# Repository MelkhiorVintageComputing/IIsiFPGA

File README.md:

# A FPGA on a IIsi PDS card...

## Goal

The goal of this repository is to be able to interface a modern (2023 era) [FPGA](https://en.wikipedia.org/wiki/Field-programmable_gate_array) with a [Macintosh IIsi](https://en.wikipedia.org/wiki/Macintosh_IIsi) using its PDS (Processor Direct Slot) connector. The PDS is basically just a physical connector to the MC68030 memory bus.

So unless you're a retrocomputing enthusiast with such a machine, this is useless. If you are such an enthusiast, then maybe the ability to connect a modern LCD monitor using a digital interface to an old Macintosh might be of interest to you.

This project was 'spun off' the [NuBusFPGA](https://github.com/rdolbeau/NuBusFPGA), a similar project for the NuBus used in several models of Macintosh of the era. NuBusFPGA itself is a spin-off of the [SBusFPGA](https://github.com/rdolbeau/SBusFPGA), a similar project for the SBus used in Sun's SPARCstation.

## Current status

The HDMI (Highly Desirable Macintosh Interface) is working, with both video (single-hardware-res, multi-depth, windowboxed lower res) & audio working. More details are available in the readme of the NuBusFPGA repository.

There's also experimental support to expose 240 MiB of DDR3 as additional memory to the host system, but that requires a patched ROM, typically using a modern Flash-based 'ROM SIMM'. Burst reads are supported for that use case, reading 16 bytes at a time from the DDR3 using a dedicated port, giving X-1-1-1 burst timings.

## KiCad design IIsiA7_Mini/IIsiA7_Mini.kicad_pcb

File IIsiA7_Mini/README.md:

# IIsiA7 Mini

## Known issues in V3.0

* The JTAG header is not wired as intended (doesn't follow any pinouts I know), but the silkscreen is correct and it can be used just fine
* Pinout silkscreen for leds D4 and D5 is switched (D4 <=> D6), D6 is really top and D4 bottom)
* IRQs and CACHE should have had pull (up for IRQs, down for CACHE), the gateware currently enables pulling at the FPGA pins

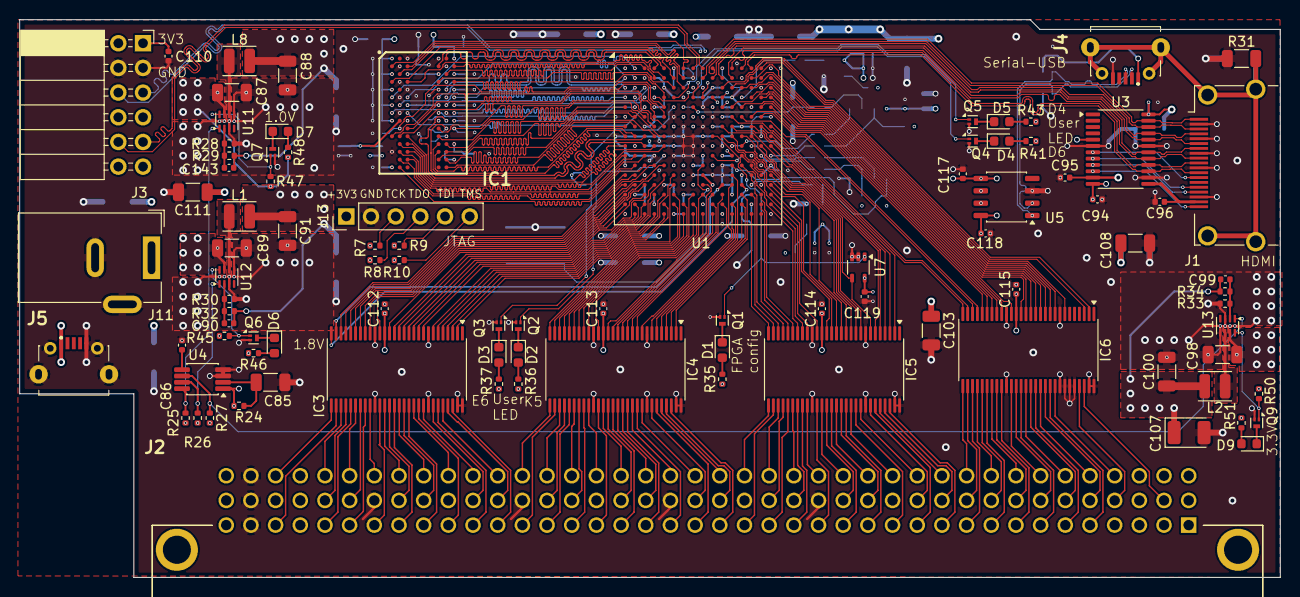
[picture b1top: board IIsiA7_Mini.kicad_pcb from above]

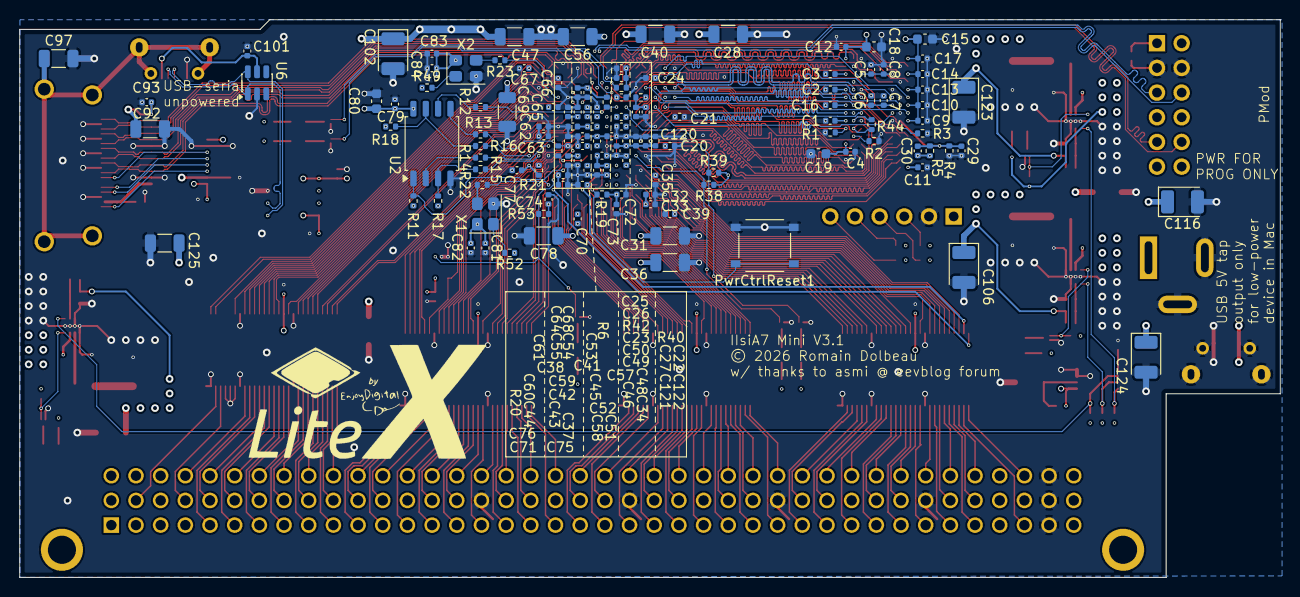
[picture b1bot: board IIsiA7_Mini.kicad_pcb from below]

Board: 6 copper layers, 129.8 x 57.4 mm, 221 parts (130 on the bottom side), 326 nets.

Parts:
C1, C2, C3, C4, C5, C6, C7, C8, C9, C10, C11, C12, C13, C14, C16, C17, C29, C30, C79, C81, C82, C83, C84, C94, C95, C96, C101, C110, C112, C113, C114, C115, C117, C118, C119: 100nF 0402; C_0402_1005Metric
C15, C18, C19, C80: 1uF 0603; C_0603_1608Metric
C20, C21, C22, C23, C24, C25, C31, C33, C34, C35, C37, C41, C42, C43, C45, C48, C49, C50, C51, C52, C53, C54, C55, C60, C63, C65, C66, C67, C68, C70, C72, C74, C75, C76, C77, C121: 470nF 0402; C_0402_1005Metric
C26, C27, C32, C38, C44, C46, C57, C58, C59, C61, C62, C64, C71, C73, C120, C122: 4.7uF 0402; C_0402_1005Metric
C28, C36, C39, C40, C47, C56, C69, C78: 100uF 1206; C_1206_3216Metric
C85, C87, C88, C89, C91, C93, C98, C100, C103, C108, C111, C125: 22uF 25V 1206; C_1206_3216Metric
C86, C92: 10nF 0402; C_0402_1005Metric
C90, C99, C143: 120pF C0G 0402; C_0402_1005Metric
C97: 1nF >=1kV 1206; C_1206_3216Metric
C102, C106, C123: 330uF CASE-B Tantalum 2.5V; CP_EIA-3528-21_Kemet-B
C107, C116, C124: 150uF CASE-B Tantalum 6.3V; CP_EIA-3528-21_Kemet-B
D1, D2, D3, D4, D5, D6, D7, D9: LED 0603; LED_0603_1608Metric
GRAPHIC1: LogoLitex; litex_logo
IC1: MT47H128M16RT-25E_C_TR; BGA84C80P9X15_900X1250X120
IC3, IC4, IC5, IC6: 74CB3T16211DGGR; TSSOP-56_6.1x14mm_P0.5mm
J1: 10029449-111RLF (HDMI A); HDMI_A_Amphenol_10029449-111
J2: 650906-5; 6509065
J3: PMod 2x6 pins, 2.54mm 90° socket; PinSocket_2x06_P2.54mm_Horizontal
J4, J5: USB Micro-B; MICROXNJ
J11: Barrel_Jack_Switch; BarrelJack_Wuerth_6941xx301002
J13: Conn_01x06_Pin; PinHeader_1x06_P2.54mm_Vertical
L1, L2, L8: 470nH 6.5A 322512; L_Changjiang_FTC322512S
PwrCtrlReset1: TS-1187A-B-A-B; SW_SPST_TS-1187A
Q1, Q2, Q3, Q4, Q5, Q6, Q7, Q9: AP1606; Diodes_DFN1006-3
R1, R2, R3, R11, R17, R18, R19, R20, R53: 4.7kΩ 0402; R_0402_1005Metric
R4, R5: 1kΩ 0402 0.1%; R_0402_1005Metric
R6, R21, R49, R52: 0Ω 0402; R_0402_1005Metric
R7, R8, R9, R10, R24, R38, R39, R40, R42, R45, R47, R50: 10kΩ 0402; R_0402_1005Metric
R12, R13, R14, R15, R16: 49.9Ω 0402 1%; R_0402_1005Metric
R22, R23: 33Ω 0402 1%; R_0402_1005Metric
R25, R26, R27: 100kΩ 0402; R_0402_1005Metric
R28: 66.5kΩ 0402 0.1%; R_0402_1005Metric
R29, R32, R34: 100kΩ 0402 0.1%; R_0402_1005Metric
R30: 200kΩ 0402 0.1%; R_0402_1005Metric
R31: 1MΩ 500V 1206; R_1206_3216Metric
R33: 453kΩ 0402 0.1%; R_0402_1005Metric
R35, R36, R37, R41, R43: 510Ω 0402; R_0402_1005Metric
R44: 100Ω 0402 0.1%; R_0402_1005Metric
R46, R48, R51: 1kΩ 0402; R_0402_1005Metric
U1: XC7A100T-FTG256; Xilinx_FTG256
U2: W25Q128JVS; SOIC-8_5.3x5.3mm_P1.27mm
U3: TPD12S016PWR; TSSOP-24_4.4x7.8mm_P0.65mm
U4: LM3881MM; VSSOP-8_3x3mm_P0.65mm
U5: CH340N; JEITA_SOIC-8_3.9x4.9mm_P1.27mm
U6: SRV05-4; SOT-23-6
U7: 74LVC1G125DCK; Texas_R-PDSO-G5_DCK-5
U11, U12, U13: TPS62823DLCR; Texas_VSON-HR-8_1.5x2mm_P0.5mm
X1, X2: ASE-xxxMHz; Oscillator_SMD_Abracon_ASE-4Pin_3.2x2.5mm

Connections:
+1V0: C45.1, C46.1, C47.1, C48.1, C49.1, C50.1, C51.1, C52.1, C53.1, C54.1, C55.1, C56.1, C57.1, C58.1, C59.1, C61.1, C88.1, C102.1, C120.1, C121.1, C122.1, C123.1, C143.2, L8.2, R28.2, U1.E10 (VCCBRAM), U1.F7 (VCCINT), U1.F9 (VCCINT), U1.F11 (VCCBRAM), U1.G6 (VCCINT), U1.H9 (VCCINT), U1.J6 (VCCINT), U1.K9 (VCCINT), U1.L8 (VCCINT)
+1V8: C1.1, C2.1, C3.1, C4.1, C5.1, C6.1, C7.1, C8.1, C9.1, C10.1, C11.1, C12.1, C13.1, C14.1, C15.1, C16.1, C17.1, C18.1, C19.1, C20.1, C21.1, C22.1, C23.1, C24.1, C25.1, C26.1, C27.1, C28.1, C30.1, C37.1, C38.1, C40.1, C41.1, C42.1, C43.1, C44.1, C90.2, C91.1, C106.1, IC1.A1 (VDD_1), IC1.A9 (VDDQ_1), IC1.C1 (VDDQ_2), IC1.C3 (VDDQ_3), IC1.C7 (VDDQ_4), IC1.C9 (VDDQ_5), IC1.E1 (VDD_2), IC1.E9 (VDDQ_6), IC1.G1 (VDDQ_7), IC1.G3 (VDDQ_8), IC1.G7 (VDDQ_9), IC1.G9 (VDDQ_10), IC1.J1 (VDDL), IC1.J9 (VDD_3), IC1.M9 (VDD_4), IC1.R1 (VDD_5), L1.2, R5.1, R30.2, R38.1, R39.1, R40.1, R42.1, U1.A6 (VCCO_35), U1.B3 (VCCO_35), U1.D7 (VCCO_35), U1.E4 (VCCO_35), U1.F1 (VCCO_35), U1.F8 (VCCBATT_0), U1.G8 (VCCADC_0), U1.G10 (VCCAUX), U1.J2 (VCCO_35), U1.J10 (VCCAUX), U1.K11 (VCCAUX), U1.L10 (VCCAUX)
+3V3: C31.1, C32.1, C33.1, C34.1, C35.1, C36.1, C39.1, C60.1, C62.1, C63.1, C64.1, C65.1, C66.1, C67.1, C68.1, C69.1, C70.1, C71.1, C72.1, C73.1, C74.1, C75.1, C76.1, C77.1, C78.1, C79.1, C80.1, C81.1, C82.1, C83.1, C84.1, C92.1, C93.1, C94.1, C99.2, C100.1, C103.1, C107.1, C108.1, C110.1, C111.1, C112.1, C113.1, C114.1, C115.1, C117.1, C118.1, C119.1, C125.1, IC3.17 (VCC), IC4.17 (VCC), IC5.17 (VCC), IC6.17 (VCC), J3.1, J3.2, J13.1, L2.2, R6.2, R7.1, R8.1, R9.1, R10.1, R11.2, R17.2, R18.2, R19.2, R20.2, R21.2, R33.2, R35.2, R36.2, R37.2, R41.2, R43.2, R49.1, R52.1, R53.2, U1.A16 (VCCO_15), U1.B13 (VCCO_15), U1.C10 (VCCO_15), U1.E14 (VCCO_15), U1.H15 (VCCO_15), U1.J12 (VCCO_15), U1.L6 (VCCO_0), U1.L16 (VCCO_14), U1.M3 (VCCO_34), U1.M9 (M0_0), U1.M13 (VCCO_14), U1.N10 (VCCO_14), U1.P7 (VCCO_14), U1.R4 (VCCO_34), U1.R14 (VCCO_14), U1.T1 (VCCO_34), U1.T11 (VCCO_14), U2.8 (VCC), U3.5 (LS_OE), U3.12 (CT_HPD), U3.24 (VCCA), U5.5 (VCC), U5.8 (V3), U7.5 (VCC), X1.4 (Vdd), X2.4 (Vdd)
+5V: C87.1, C89.1, C95.1, C98.1, C116.1, C124.1, J2.A37, J2.B13, J2.B19, J2.B25, J2.B31, J2.B37, J2.C37, J5.1 (VBUS), J11.1, R24.2, R25.2, R26.2, R27.2, R45.1, R46.2, R47.1, R48.2, R50.1, R51.2, U3.11 (VCC5V), U4.1 (VCC), U11.7 (VIN), U12.7 (VIN), U13.7 (VIN)
/Artix-7 Bank 14+15/CLK_54_000: R23.1, U1.D13 (IO_L12P_T1_MRCC_15)
/Artix-7 Bank 14+15/CLK_100_000: R22.1, U1.N14 (IO_L12P_T1_MRCC_14)
/Artix-7 Bank 34+35/IO_0_35: Q3.1 (G), R39.2, U1.E6 (IO_0_35)
/Artix-7 Bank 34+35/IO_25_35: Q2.1 (G), R38.2, U1.K5 (IO_25_35)
/Artix-7 Bank 34+35/IO_L6P_T0_35: Q5.1 (G), R42.2, U1.D6 (IO_L6P_T0_35)
/Artix-7 Bank 34+35/IO_L12P_T1_MRCC_35: Q4.1 (G), R40.2, U1.D4 (IO_L12P_T1_MRCC_35)
/Artix-7 Bank 34+35/ddr2/DDR2_CS: IC1.L8 (CS#), R2.1
/Artix-7 Support/CCLK_0: R12.1, U1.E8 (CCLK_0)
/Artix-7 Support/FPGA flash/CLK: R12.2, U2.6 (CLK)
/Artix-7 Support/FPGA flash/IO_{0}: R13.2, U2.5 (DI/IO_{0})
/Artix-7 Support/FPGA flash/IO_{1}: R14.2, U2.2 (DO/IO_{1})
/Artix-7 Support/FPGA flash/IO_{2}: R15.2, R17.1, U2.3 (~WP/IO_{2})
/Artix-7 Support/FPGA flash/IO_{3}: R16.2, R18.1, U2.7 (~HOLD/~RESET/IO_{3})
/Artix-7 Support/INIT_B_0: R20.1, U1.K10 (INIT_B_0)
/Artix-7 Support/PROGRAM_B_0: PwrCtrlReset1.1, R19.1, U1.L9 (PROGRAM_B_0)
/Artix-7 Support/TCK_0: J13.3, R7.2, U1.L7 (TCK_0)
/Artix-7 Support/TDI_0: J13.5, R9.2, U1.N7 (TDI_0)
/Artix-7 Support/TDO_0: J13.4, R8.2, U1.N8 (TDO_0)
/Artix-7 Support/TMS_0: J13.6, R10.2, U1.M7 (TMS_0)
/Board Specific/HDMI (Highly Desirable Macintosh Interface)/HDMI_5V: C96.1, J1.18 (+5V), U3.13 (5V_OUT)
/Board Specific/HDMI (Highly Desirable Macintosh Interface)/HDMI_CEC_B: J1.13 (CEC), U3.7 (CEC_B)
/Board Specific/HDMI (Highly Desirable Macintosh Interface)/HDMI_HPD_B: J1.19 (HPD), U3.10 (HPD_B)
/Board Specific/HDMI (Highly Desirable Macintosh Interface)/HDMI_SCL_B: J1.15 (SCL), U3.8 (SCL_B)
/Board Specific/HDMI (Highly Desirable Macintosh Interface)/HDMI_SDA_B: J1.16 (SDA), U3.9 (SDA_B)
/Board Specific/serial_usb/USB_D+: J4.3 (D+), U5.1 (UD+), U6.6 (IO4)
/Board Specific/serial_usb/USB_D-: J4.2 (D-), U5.2 (UD-), U6.1 (IO1)
/Board Specific/serial_usb/Vbus: C101.1, J4.1 (VBUS), U6.5 (VP)
/FLAG1: R25.1, U4.8 (FLAG1), U11.1 (EN)
/FLAG2: R26.1, U4.7 (FLAG2), U12.1 (EN)
/FLAG3: R27.1, U4.6 (FLAG3), U13.1 (EN)
/PWRGOOD_1V0: Q7.1 (G), R47.2, U11.8 (PG)
/PWRGOOD_1V8: Q6.1 (G), R45.2, U12.8 (PG)
/PWRGOOD_3V3: Q9.1 (G), R50.2, U13.8 (PG)
/PWRGOOD_5V: C85.1, R24.1, U4.2 (EN)
/power_rail_1V0/FB: C143.1, R28.1, R29.2, U11.2 (FB)
/power_rail_1V0/SW: L8.1, U11.6 (SW)
/power_rail_1V8/FB: C90.1, R30.1, R32.2, U12.2 (FB)
/power_rail_1V8/SW: L1.1, U12.6 (SW)
/power_rail_3V3/FB: C99.1, R33.1, R34.2, U13.2 (FB)
/power_rail_3V3/SW: L2.1, U13.6 (SW)
A0_3V3: IC3.26 (2A10), U1.M1 (IO_L2N_T0_34)
A0_5V: IC3.31 (2B10), J2.C36
A1_3V3: IC3.25 (2A9), U1.M2 (IO_L2P_T0_34)
A1_5V: IC3.32 (2B9), J2.B36
A2_3V3: IC3.24 (2A8), U1.L4 (IO_L1P_T0_34)
A2_5V: IC3.33 (2B8), J2.A36
A3_3V3: IC3.23 (2A7), U1.N1 (IO_L4P_T0_34)
A3_5V: IC3.34 (2B7), J2.C35
A4_3V3: IC3.22 (2A6), U1.L5 (IO_0_34)
A4_5V: IC3.35 (2B6), J2.B35
A5_3V3: IC3.21 (2A5), U1.N2 (IO_L3N_T0_DQS_34)
A5_5V: IC3.36 (2B5), J2.A35
A6_3V3: IC3.20 (2A4), U1.P1 (IO_L4N_T0_34)
A6_5V: IC3.37 (2B4), J2.C34
A7_3V3: IC3.18 (2A3), U1.M4 (IO_L1N_T0_34)
A7_5V: IC3.39 (2B3), J2.A34
A8_3V3: IC3.16 (2A2), U1.N3 (IO_L3P_T0_DQS_34)
A8_5V: IC3.40 (2B2), J2.C33
A9_3V3: IC3.15 (2A1), U1.R1 (IO_L7N_T1_34)
A9_5V: IC3.41 (2B1), J2.B33
A10_3V3: IC3.14 (1A12), U1.P3 (IO_L5N_T0_34)
A10_5V: IC3.42 (1B12), J2.A33
A11_3V3: IC3.13 (1A11), U1.N4 (IO_L6N_T0_VREF_34)
A11_5V: IC3.43 (1B11), J2.C32
A12_3V3: IC3.12 (1A10), U1.T2 (IO_L8N_T1_34)
A12_5V: IC3.44 (1B10), J2.B32
A13_3V3: IC3.11 (1A9), U1.R2 (IO_L7P_T1_34)
A13_5V: IC3.45 (1B9), J2.A32
A14_3V3: IC3.10 (1A8), U1.R3 (IO_L8P_T1_34)
A14_5V: IC3.46 (1B8), J2.C31
A15_3V3: IC3.9 (1A7), U1.T3 (IO_L9N_T1_DQS_34)
A15_5V: IC3.47 (1B7), J2.A31
A16_3V3: IC3.7 (1A6), U1.M5 (IO_L6P_T0_34)
A16_5V: IC3.48 (1B6), J2.C30
A17_3V3: IC3.6 (1A5), U1.P4 (IO_L5P_T0_34)
A17_5V: IC3.50 (1B5), J2.B30
A18_3V3: IC3.5 (1A4), U1.T4 (IO_L9P_T1_DQS_34)
A18_5V: IC3.51 (1B4), J2.A30
A19_3V3: IC3.4 (1A3), U1.P5 (IO_L10P_T1_34)
A19_5V: IC3.52 (1B3), J2.C29
A20_3V3: IC3.3 (1A2), U1.M6 (IO_L19P_T3_A10_D26_14)
A20_5V: IC3.53 (1B2), J2.B29
A21_3V3: IC3.2 (1A1), U1.T5 (IO_L23N_T3_A02_D18_14)
A21_5V: IC3.54 (1B1), J2.A29
A22_3V3: IC4.28 (2A12), U1.R5 (IO_L23P_T3_A03_D19_14)
A22_5V: IC4.29 (2B12), J2.C28
A23_3V3: IC4.27 (2A11), U1.N6 (IO_L19N_T3_A09_D25_VREF_14)
A23_5V: IC4.30 (2B11), J2.A28
A24_3V3: IC4.26 (2A10), U1.R6 (IO_L24P_T3_A01_D17_14)
A24_5V: IC4.31 (2B10), J2.C27
A25_3V3: IC4.25 (2A9), U1.P6 (IO_25_14)
A25_5V: IC4.32 (2B9), J2.B27
A26_3V3: IC4.24 (2A8), U1.T7 (IO_L21P_T3_DQS_14)
A26_5V: IC4.33 (2B8), J2.A27
A27_3V3: IC4.23 (2A7), U1.R7 (IO_L24N_T3_A00_D16_14)
A27_5V: IC4.34 (2B7), J2.C26
A28_3V3: IC4.22 (2A6), U1.P8 (IO_L20P_T3_A08_D24_14)
A28_5V: IC4.35 (2B6), J2.B26
A29_3V3: IC4.21 (2A5), U1.T8 (IO_L21N_T3_DQS_A06_D22_14)
A29_5V: IC4.36 (2B5), J2.A26
A30_3V3: IC4.20 (2A4), U1.R8 (IO_L20N_T3_A07_D23_14)
A30_5V: IC4.37 (2B4), J2.C25
A31_3V3: IC4.18 (2A3), U1.P9 (IO_L18N_T2_A11_D27_14)
A31_5V: IC4.39 (2B3), J2.A25
APMOD0-56+: J3.6, U1.E11 (IO_L14P_T2_SRCC_15)
APMOD0-56-: J3.5, U1.D11 (IO_L14N_T2_SRCC_15)
APMOD0-78+: J3.8, U1.D8 (IO_L6P_T0_15)
APMOD0-78-: J3.7, U1.D9 (IO_L6N_T0_VREF_15)
APMOD0-910+: J3.10, U1.A8 (IO_L2P_T0_AD8P_15)
APMOD0-910-: J3.9, U1.A9 (IO_L2N_T0_AD8N_15)
APMOD0-1112+: J3.12, U1.C8 (IO_L1P_T0_AD0P_15)
APMOD0-1112-: J3.11, U1.C9 (IO_L1N_T0_AD0N_15)
C16M_3V3: IC3.28 (2A12), U1.N13 (IO_L11P_T1_SRCC_14)
C16M_5V: IC3.29 (2B12), J2.C38
CACHE_3V3: IC6.2 (1A1), U1.C11 (IO_L11P_T1_SRCC_15)
CACHE_5V: IC6.54 (1B1), J2.B2
CPUCLK_3V3: IC3.27 (2A11), U1.N11 (IO_L13P_T2_MRCC_14)
CPUCLK_5V: IC3.30 (2B11), J2.A38
D0_3V3: IC5.9 (1A7), U1.J15 (IO_L23P_T3_FOE_B_15)
D0_5V: IC5.47 (1B7), J2.A13
D1_3V3: IC5.10 (1A8), U1.H14 (IO_L24P_T3_RS1_15)
D1_5V: IC5.46 (1B8), J2.C13
D2_3V3: IC5.11 (1A9), U1.H13 (IO_L20N_T3_A19_15)
D2_5V: IC5.45 (1B9), J2.A14
D3_3V3: IC5.12 (1A10), U1.H12 (IO_L20P_T3_A20_15)
D3_5V: IC5.44 (1B10), J2.B14
D4_3V3: IC5.13 (1A11), U1.M16 (IO_L7P_T1_D09_14)
D4_5V: IC5.43 (1B11), J2.C14
D5_3V3: IC5.14 (1A12), U1.H11 (IO_L19P_T3_A22_15)
D5_5V: IC5.42 (1B12), J2.A15
D6_3V3: IC5.15 (2A1), U1.N16 (IO_L7N_T1_D10_14)
D6_5V: IC5.41 (2B1), J2.B15
D7_3V3: IC5.16 (2A2), U1.K13 (IO_L5P_T0_D06_14)
D7_5V: IC5.40 (2B2), J2.C15
D8_3V3: IC5.18 (2A3), U1.P16 (IO_L8N_T1_D12_14)
D8_5V: IC5.39 (2B3), J2.A16
D9_3V3: IC5.20 (2A4), U1.L14 (IO_L4P_T0_D04_14)
D9_5V: IC5.37 (2B4), J2.C16
D10_3V3: IC5.21 (2A5), U1.R16 (IO_L9N_T1_DQS_D13_14)
D10_5V: IC5.36 (2B5), J2.A17
D11_3V3: IC5.22 (2A6), U1.L13 (IO_L5N_T0_D07_14)
D11_5V: IC5.35 (2B6), J2.B17
D12_3V3: IC5.23 (2A7), U1.P15 (IO_L8P_T1_D11_14)
D12_5V: IC5.34 (2B7), J2.C17
D13_3V3: IC5.24 (2A8), U1.R15 (IO_L9P_T1_DQS_14)
D13_5V: IC5.33 (2B8), J2.A18
D14_3V3: IC5.25 (2A9), U1.T15 (IO_L10N_T1_D15_14)
D14_5V: IC5.32 (2B9), J2.B18
D15_3V3: IC5.26 (2A10), U1.M14 (IO_L4N_T0_D05_14)
D15_5V: IC5.31 (2B10), J2.C18
D16_3V3: IC5.27 (2A11), U1.P14 (IO_L12N_T1_MRCC_14)
D16_5V: IC5.30 (2B11), J2.A19
D17_3V3: IC5.28 (2A12), U1.T14 (IO_L10P_T1_D14_14)
D17_5V: IC5.29 (2B12), J2.C19
D18_3V3: IC4.2 (1A1), U1.P13 (IO_L11N_T1_SRCC_14)
D18_5V: IC4.54 (1B1), J2.A20
D19_3V3: IC4.3 (1A2), U1.R13 (IO_L16P_T2_CSI_B_14)
D19_5V: IC4.53 (1B2), J2.B20
D20_3V3: IC4.4 (1A3), U1.T13 (IO_L16N_T2_A15_D31_14)
D20_5V: IC4.52 (1B3), J2.C20
D21_3V3: IC4.5 (1A4), U1.M12 (IO_L6N_T0_D08_VREF_14)
D21_5V: IC4.51 (1B4), J2.A21
D22_3V3: IC4.6 (1A5), U1.R12 (IO_L15P_T2_DQS_RDWR_B_14)
D22_5V: IC4.50 (1B5), J2.B21
D23_3V3: IC4.7 (1A6), U1.T12 (IO_L15N_T2_DQS_DOUT_CSO_B_14)
D23_5V: IC4.48 (1B6), J2.C21
D24_3V3: IC4.9 (1A7), U1.N12 (IO_L13N_T2_MRCC_14)
D24_5V: IC4.47 (1B7), J2.A22
D25_3V3: IC4.10 (1A8), U1.R11 (IO_L17N_T2_A13_D29_14)
D25_5V: IC4.46 (1B8), J2.C22
D26_3V3: IC4.11 (1A9), U1.P11 (IO_L14N_T2_SRCC_14)
D26_5V: IC4.45 (1B9), J2.A23
D27_3V3: IC4.12 (1A10), U1.R10 (IO_L17P_T2_A14_D30_14)
D27_5V: IC4.44 (1B10), J2.B23
D28_3V3: IC4.13 (1A11), U1.T10 (IO_L22N_T3_A04_D20_14)
D28_5V: IC4.43 (1B11), J2.C23
D29_3V3: IC4.14 (1A12), U1.P10 (IO_L14P_T2_SRCC_14)
D29_5V: IC4.42 (1B12), J2.A24
D30_3V3: IC4.15 (2A1), U1.N9 (IO_L18P_T2_A12_D28_14)
D30_5V: IC4.41 (2B1), J2.B24
D31_3V3: IC4.16 (2A2), U1.T9 (IO_L22P_T3_A05_D21_14)
D31_5V: IC4.40 (2B2), J2.C24
DDR2_A0: IC1.M8 (A0), U1.H5 (IO_L18P_T2_35)
DDR2_A1: IC1.M3 (A1), U1.J4 (IO_L19N_T3_VREF_35)
DDR2_A2: IC1.M7 (A2), U1.H1 (IO_L20N_T3_35)
DDR2_A3: IC1.N2 (A3), U1.K2 (IO_L24N_T3_35)
DDR2_A4: IC1.N8 (A4), U1.F2 (IO_L15P_T2_DQS_35)
DDR2_A5: IC1.N3 (A5), U1.K1 (IO_L22P_T3_35)
DDR2_A6: IC1.N7 (A6), U1.H2 (IO_L20P_T3_35)
DDR2_A7: IC1.P2 (A7), U1.L2 (IO_L23N_T3_35)
DDR2_A8: IC1.P8 (A8), U1.G2 (IO_L17P_T2_35)
DDR2_A9: IC1.P3 (A9), U1.K3 (IO_L24P_T3_35)
DDR2_A10: IC1.M2 (A10), U1.J5 (IO_L19P_T3_35)
DDR2_A11: IC1.P7 (A11), U1.H4 (IO_L18N_T2_35)
DDR2_A12: IC1.R2 (A12), U1.L3 (IO_L23P_T3_35)
DDR2_A13: IC1.R8 (A13), U1.G1 (IO_L17N_T2_35)
DDR2_BA0: IC1.L2 (BA0), U1.G5 (IO_L16P_T2_35)
DDR2_BA1: IC1.L3 (BA1), U1.J1 (IO_L22N_T3_35)
DDR2_BA2: IC1.L1 (BA2), U1.F5 (IO_L13P_T2_MRCC_35)
DDR2_CAS: IC1.L7 (CAS#), U1.E1 (IO_L15N_T2_DQS_35)
DDR2_CKE: IC1.K2 (CKE), R3.1, U1.E5 (IO_L13N_T2_MRCC_35)
DDR2_CLK_N: IC1.K8 (CK#), R44.1, U1.H3 (IO_L21N_T3_DQS_35)
DDR2_CLK_P: IC1.J8 (CK), R44.2, U1.J3 (IO_L21P_T3_DQS_35)
DDR2_DM0: IC1.F3 (LDM), U1.B2 (IO_L8P_T1_AD14P_35)
DDR2_DM1: IC1.B3 (UDM), U1.B7 (IO_L1P_T0_AD4P_35)
DDR2_DQ0: IC1.G8 (DQ0), U1.D1 (IO_L10N_T1_AD15N_35)
DDR2_DQ1: IC1.G2 (DQ1), U1.C2 (IO_L7N_T1_AD6N_35)
DDR2_DQ2: IC1.H7 (DQ2), U1.E2 (IO_L10P_T1_AD15P_35)
DDR2_DQ3: IC1.H3 (DQ3), U1.E3 (IO_L11P_T1_SRCC_35)
DDR2_DQ4: IC1.H1 (DQ4), U1.C4 (IO_L12N_T1_MRCC_35)
DDR2_DQ5: IC1.H9 (DQ5), U1.D3 (IO_L11N_T1_SRCC_35)
DDR2_DQ6: IC1.F1 (DQ6), U1.A2 (IO_L8N_T1_AD14N_35)
DDR2_DQ7: IC1.F9 (DQ7), U1.C3 (IO_L7P_T1_AD6P_35)
DDR2_DQ8: IC1.C8 (DQ8), U1.A3 (IO_L4N_T0_35)
DDR2_DQ9: IC1.C2 (DQ9), U1.C7 (IO_L5P_T0_AD13P_35)
DDR2_DQ10: IC1.D7 (DQ10), U1.C6 (IO_L5N_T0_AD13N_35)
DDR2_DQ11: IC1.D3 (DQ11), U1.B5 (IO_L2N_T0_AD12N_35)
DDR2_DQ12: IC1.D1 (DQ12), U1.B6 (IO_L2P_T0_AD12P_35)
DDR2_DQ13: IC1.D9 (DQ13), U1.D5 (IO_L6N_T0_VREF_35)
DDR2_DQ14: IC1.B1 (DQ14), U1.A7 (IO_L1N_T0_AD4N_35)
DDR2_DQ15: IC1.B9 (DQ15), U1.B4 (IO_L4P_T0_35)
DDR2_DQS0_N: IC1.E8 (LDQS#/NU), U1.B1 (IO_L9N_T1_DQS_AD7N_35)
DDR2_DQS0_P: IC1.F7 (LDQS), U1.C1 (IO_L9P_T1_DQS_AD7P_35)
DDR2_DQS1_N: IC1.A8 (UDQS#/NU), U1.A4 (IO_L3N_T0_DQS_AD5N_35)
DDR2_DQS1_P: IC1.B7 (UDQS), U1.A5 (IO_L3P_T0_DQS_AD5P_35)
DDR2_ODT: IC1.K9 (ODT), R1.1, U1.F3 (IO_L14N_T2_SRCC_35)
DDR2_RAS: IC1.K7 (RAS#), U1.G4 (IO_L16N_T2_35)
DDR2_VREF: C29.1, C30.2, IC1.J2 (VREF), R4.1, R5.2
DDR2_WE: IC1.K3 (WE#), U1.F4 (IO_L14P_T2_SRCC_35)
DONE_0: Q1.1 (G), R53.1, U1.H10 (DONE_0), U7.1
FC0_3V3: IC5.4 (1A3), U1.G14 (IO_L21P_T3_DQS_15)
FC0_5V: IC5.52 (1B3), J2.C11
FC1_3V3: IC5.3 (1A2), U1.H16 (IO_L22P_T3_A17_15)
FC1_5V: IC5.53 (1B2), J2.B11
FC2_3V3: IC5.2 (1A1), U1.G15 (IO_L24N_T3_RS0_15)
FC2_5V: IC5.54 (1B1), J2.A11
GND: C1.2, C2.2, C3.2, C4.2, C5.2, C6.2, C7.2, C8.2, C9.2, C10.2, C11.2, C12.2, C13.2, C14.2, C15.2, C16.2, C17.2, C18.2, C19.2, C20.2, C21.2, C22.2, C23.2, C24.2, C25.2, C26.2, C27.2, C28.2, C29.2, C31.2, C32.2, C33.2, C34.2, C35.2, C36.2, C37.2, C38.2, C39.2, C40.2, C41.2, C42.2, C43.2, C44.2, C45.2, C46.2, C47.2, C48.2, C49.2, C50.2, C51.2, C52.2, C53.2, C54.2, C55.2, C56.2, C57.2, C58.2, C59.2, C60.2, C61.2, C62.2, C63.2, C64.2, C65.2, C66.2, C67.2, C68.2, C69.2, C70.2, C71.2, C72.2, C73.2, C74.2, C75.2, C76.2, C77.2, C78.2, C79.2, C80.2, C81.2, C82.2, C83.2, C84.2, C85.2, C86.2, C87.2, C88.2, C89.2, C91.2, C92.2, C93.2, C94.2, C95.2, C96.2, C97.2, C98.2, C100.2, C101.2, C102.2, C103.2, C106.2, C107.2, C108.2, C110.2, C111.2, C112.2, C113.2, C114.2, C115.2, C116.2, C117.2, C118.2, C119.2, C120.2, C121.2, C122.2, C123.2, C124.2, C125.2, IC1.A3 (VSS_1), IC1.A7 (VSSQ_1), IC1.B2 (VSSQ_2), IC1.B8 (VSSQ_3), IC1.D2 (VSSQ_4), IC1.D8 (VSSQ_5), IC1.E3 (VSS_2), IC1.E7 (VSSQ_6), IC1.F2 (VSSQ_7), IC1.F8 (VSSQ_8), IC1.H2 (VSSQ_9), IC1.H8 (VSSQ_10), IC1.J3 (VSS_3), IC1.J7 (VSSDL), IC1.N1 (VSS_4), IC1.P9 (VSS_5), IC3.8 (GND_1), IC3.19 (GND_2), IC3.38 (GND_3), IC3.49 (GND_4), IC3.55 (2~OE), IC3.56 (1~OE), IC4.8 (GND_1), IC4.19 (GND_2), IC4.38 (GND_3), IC4.49 (GND_4), IC4.55 (2~OE), IC4.56 (1~OE), IC5.8 (GND_1), IC5.19 (GND_2), IC5.38 (GND_3), IC5.49 (GND_4), IC5.55 (2~OE), IC5.56 (1~OE), IC6.8 (GND_1), IC6.19 (GND_2), IC6.38 (GND_3), IC6.49 (GND_4), IC6.50 (1B5), IC6.51 (1B4), IC6.52 (1B3), IC6.55 (2~OE), IC6.56 (1~OE), J1.2 (D2S), J1.5 (D1S), J1.8 (D0S), J1.11 (CKS), J1.17 (GND), J2.A39, J2.B16, J2.B22, J2.B28, J2.B34, J2.B39, J2.C39, J3.3, J3.4, J4.5 (GND), J5.5 (GND), J5.6 (Shield), J11.2, J11.3, J13.2, PwrCtrlReset1.2, Q1.2 (S), Q2.2 (S), Q3.2 (S), Q4.2 (S), Q5.2 (S), Q6.2 (S), Q7.2 (S), Q9.2 (S), R1.2, R2.2, R3.2, R4.2, R29.1, R31.2, R32.1, R34.1, U1.A1 (GND), U1.A11 (GND), U1.B8 (GND), U1.C5 (GND), U1.C15 (GND), U1.D2 (GND), U1.D12 (GND), U1.E9 (GND), U1.F6 (GND), U1.F10 (GND), U1.F16 (GND), U1.G3 (GND), U1.G7 (GNDADC_0), U1.G9 (GND), U1.G13 (GND), U1.H6 (GND), U1.H7 (VREFN_0), U1.H8 (VP_0), U1.J7 (VN_0), U1.J8 (VREFP_0), U1.J9 (GND), U1.J11 (GND), U1.K4 (GND), U1.K6 (GND), U1.K7 (DXN_0), U1.K8 (DXP_0), U1.K14 (GND), U1.L1 (GND), U1.L11 (GND), U1.M8 (GND), U1.M10 (M1_0), U1.M11 (M2_0), U1.N5 (GND), U1.N15 (GND), U1.P2 (GND), U1.P12 (GND), U1.R9 (GND), U1.T6 (GND), U1.T16 (GND), U2.4 (GND), U3.6 (GND_6), U3.14 (GND_14), U3.19 (GND_19), U4.3 (GND), U4.4 (INV), U5.3 (GND), U6.2 (VN), U7.2, U7.3 (GND), U11.3 (AGND), U11.5 (PGND), U12.3 (AGND), U12.5 (PGND), U13.3 (AGND), U13.5 (PGND), X1.2 (GND), X2.2 (GND)
HDMI_CLK+: J1.10 (CK+), U1.A13 (IO_L7P_T1_AD2P_15), U3.16 (CLK+)
HDMI_CLK-: J1.12 (CK-), U1.A14 (IO_L7N_T1_AD2N_15), U3.15 (CLK-)
HDMI_D0+: J1.7 (D0+), U1.B12 (IO_L5P_T0_AD9P_15), U3.18 (D0+)
HDMI_D0-: J1.9 (D0-), U1.A12 (IO_L5N_T0_AD9N_15), U3.17 (D0-)
HDMI_D1+: J1.4 (D1+), U1.B10 (IO_L4P_T0_15), U3.21 (D1+)
HDMI_D1-: J1.6 (D1-), U1.B11 (IO_L4N_T0_15), U3.20 (D1-)
HDMI_D2+: J1.1 (D2+), U1.B9 (IO_L3P_T0_DQS_AD1P_15), U3.23 (D2+)
HDMI_D2-: J1.3 (D2-), U1.A10 (IO_L3N_T0_DQS_AD1N_15), U3.22 (D2-)
IO_0_14: U1.K12 (IO_0_14), U5.7 (RXD)
IO_0_15: U1.D10 (IO_0_15), U5.6 (TXD)
IO_25_15: IC5.7 (1A6), U1.G11 (IO_25_15), U7.4
IO_L8N_T1_AD10N_15: IC6.9 (1A7), U1.B14 (IO_L8N_T1_AD10N_15)
IO_L8P_T1_AD10P_15: IC6.13 (1A11), U1.C14 (IO_L8P_T1_AD10P_15)
IO_L9N_T1_DQS_AD3N_15: IC6.7 (1A6), U1.A15 (IO_L9N_T1_DQS_AD3N_15)
IO_L9P_T1_DQS_AD3P_15: IC6.10 (1A8), U1.B15 (IO_L9P_T1_DQS_AD3P_15)
IO_L10N_T1_AD11N_15: IC6.12 (1A10), U1.B16 (IO_L10N_T1_AD11N_15)
IO_L10P_T1_AD11P_15: IC6.15 (2A1), U1.C16 (IO_L10P_T1_AD11P_15)
IO_L11N_T1_SRCC_15: IC6.3 (1A2), U1.C12 (IO_L11N_T1_SRCC_15)
IO_L12N_T1_MRCC_15: IC6.11 (1A9), U1.C13 (IO_L12N_T1_MRCC_15)
IO_L13N_T2_MRCC_15: IC6.21 (2A5), U1.E13 (IO_L13N_T2_MRCC_15)
IO_L13P_T2_MRCC_15: IC6.16 (2A2), U1.E12 (IO_L13P_T2_MRCC_15)
IO_L15N_T2_DQS_ADV_B_15: IC6.18 (2A3), U1.D15 (IO_L15N_T2_DQS_ADV_B_15)
IO_L15P_T2_DQS_15: IC6.14 (1A12), U1.D14 (IO_L15P_T2_DQS_15)
IO_L16N_T2_A27_15: IC6.26 (2A10), U1.F13 (IO_L16N_T2_A27_15)
IO_L16P_T2_A28_15: IC6.28 (2A12), U1.F12 (IO_L16P_T2_A28_15)
IO_L17N_T2_A25_15: IC6.20 (2A4), U1.D16 (IO_L17N_T2_A25_15)
IO_L17P_T2_A26_15: IC6.23 (2A7), U1.E16 (IO_L17P_T2_A26_15)
IO_L18N_T2_A23_15: IC6.22 (2A6), U1.E15 (IO_L18N_T2_A23_15)
IO_L18P_T2_A24_15: IC6.25 (2A9), U1.F15 (IO_L18P_T2_A24_15)
IO_L19N_T3_A21_VREF_15: IC5.5 (1A4), U1.G12 (IO_L19N_T3_A21_VREF_15)
IO_L21N_T3_DQS_A18_15: IC6.24 (2A8), U1.F14 (IO_L21N_T3_DQS_A18_15)
IO_L22N_T3_A16_15: IC6.27 (2A11), U1.G16 (IO_L22N_T3_A16_15)
IO_L23N_T3_FWE_B_15: IC5.6 (1A5), U1.J16 (IO_L23N_T3_FWE_B_15)
IPL0_5V: IC6.45 (1B9), J2.C5
IPL1_5V: IC6.46 (1B8), J2.B5
IPL2_5V: IC6.47 (1B7), J2.A5
unnamed: D1.2 (A), R35.1
unnamed: D1.1 (K), Q1.3 (D)
unnamed: D2.2 (A), R36.1
unnamed: D2.1 (K), Q2.3 (D)
unnamed: D3.2 (A), R37.1
unnamed: D3.1 (K), Q3.3 (D)
unnamed: D4.2 (A), R41.1
unnamed: D4.1 (K), Q4.3 (D)
unnamed: D5.2 (A), R43.1
unnamed: D5.1 (K), Q5.3 (D)
unnamed: D6.2 (A), R46.1
unnamed: D6.1 (K), Q6.3 (D)
unnamed: D7.2 (A), R48.1
unnamed: D7.1 (K), Q7.3 (D)
unnamed: D9.2 (A), R51.1
unnamed: D9.1 (K), Q9.3 (D)
unnamed: R21.1, U1.L15 (IO_L3P_T0_DQS_PUDC_B_14)
unnamed: R6.1, U1.E7 (CFGBVS_0)
unnamed: C86.1, U4.5 (TADJ)
unnamed: R52.2, X1.1 (EN)
unnamed: R22.2, X1.3 (OUT)
unnamed: R49.2, X2.1 (EN)
unnamed: R23.2, X2.3 (OUT)
RMC_5V: IC6.42 (1B12), J2.C6
SHIELD: C97.1, J1.SH, J4.6 (Shield), R31.1
SIZ0_5V: IC6.33 (2B8), J2.B9
SIZ1_5V: IC6.34 (2B7), J2.A9
SPI_DQ0: R13.1, U1.J13 (IO_L1P_T0_D00_MOSI_14)
SPI_DQ1: R14.1, U1.J14 (IO_L1N_T0_D01_DIN_14)
SPI_DQ2: R15.1, U1.K15 (IO_L2P_T0_D02_14)
SPI_DQ3: R16.1, U1.K16 (IO_L2N_T0_D03_14)
SPI_~CS: R11.1, U1.L12 (IO_L6P_T0_FCS_B_14), U2.1 (~CS)
~AS_5V: IC6.32 (2B9), J2.C9
~BERR_5V: IC5.50 (1B5), J2.B12
~BGACK_5V: IC6.31 (2B10), J2.A10
~BG_5V: IC6.30 (2B11), J2.B10
~BR_5V: IC6.29 (2B12), J2.C10
~CBACK_5V: IC6.40 (2B2), J2.B7
~CBREQ_5V: IC6.39 (2B3), J2.C7
~CIOUT_5V: IC6.44 (1B10), J2.A6
~DSACK0_5V: IC6.36 (2B5), J2.B8
~DSACK1_5V: IC6.37 (2B4), J2.A8
~DS_5V: IC6.43 (1B11), J2.B6
~HALT_5V: IC5.48 (1B6), J2.C12
~IRQ1_5V: IC6.48 (1B6), J2.C4
~IRQ2_5V: IC6.53 (1B2), J2.B4
~RESET_5V: IC5.51 (1B4), J2.A12
~RW_5V: IC6.35 (2B6), J2.C8
~STERM_5V: IC6.41 (2B1), J2.A7

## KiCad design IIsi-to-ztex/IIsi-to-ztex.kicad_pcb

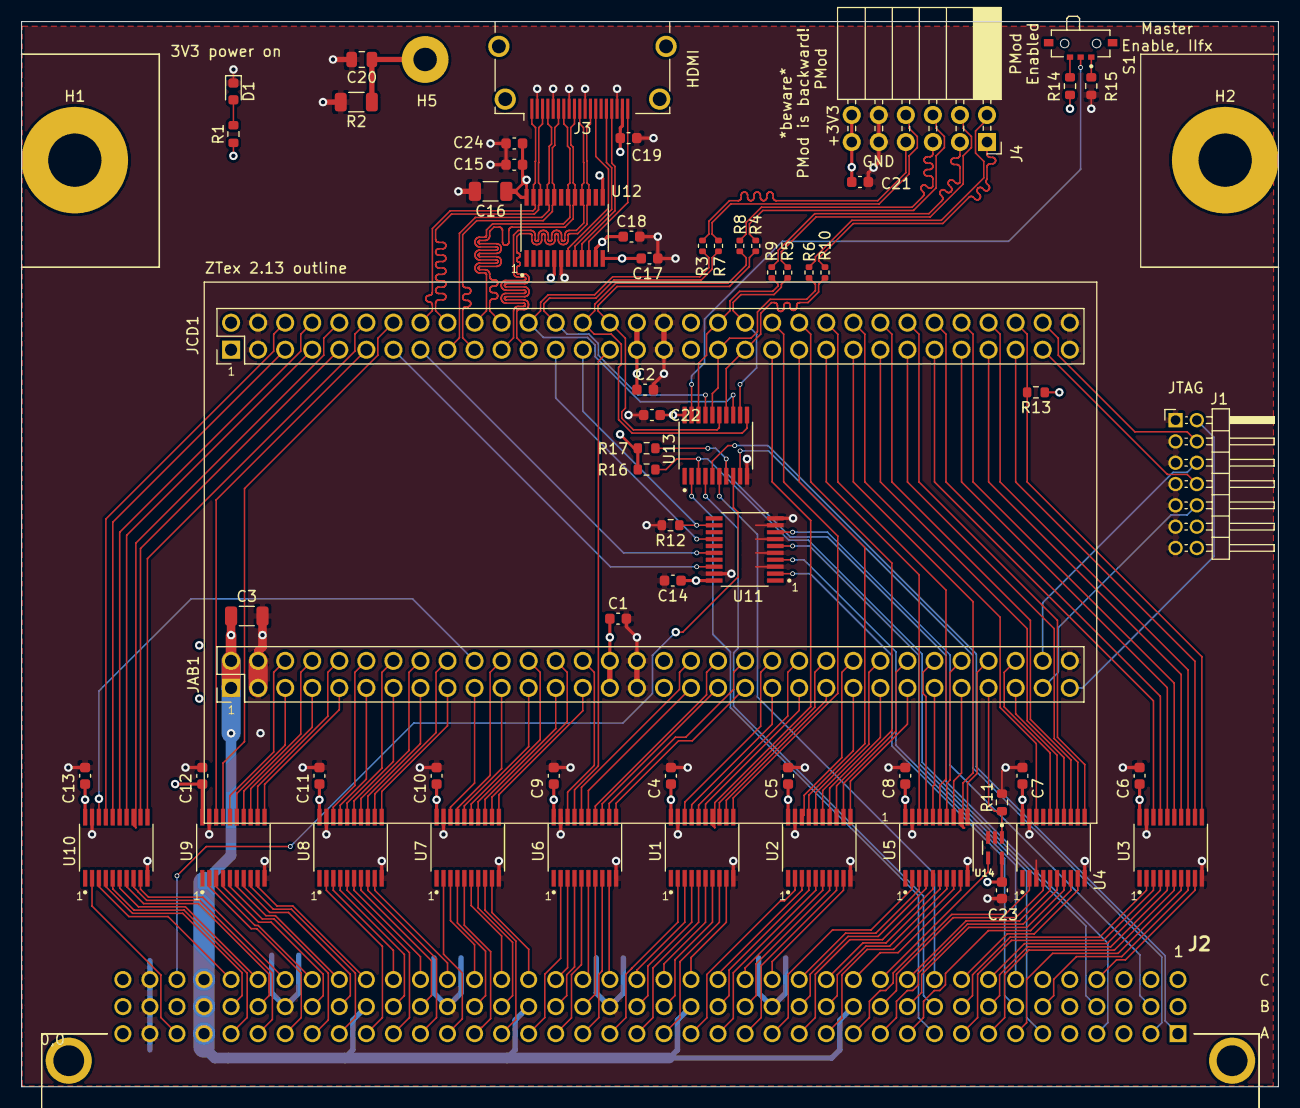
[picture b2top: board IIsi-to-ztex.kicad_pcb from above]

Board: 4 copper layers, 118.0 x 100.0 mm, 66 parts (0 on the bottom side), 218 nets.

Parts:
C1, C2, C4, C5, C6, C7, C8, C9, C10, C11, C12, C13, C14, C17, C18, C19, C21, C22, C23, C24: 100nF; C_0603_1608Metric
C3: 47uF 10V+; C_1206_3216Metric
C15: 10nF; C_0603_1608Metric
C16: 47uF 10V 1206; C_1206_3216Metric
C20: 10nF 1kV 0805; C_0805_2012Metric
D1: RED LED 0603; LED_0603_1608Metric
H1, H2: MountingHole_Pad; MountingHole_5mm_Pad
H5: MountingHole_Pad; MountingHole_2.2mm_M2_Pad
J1: Conn_02x07_Odd_Even; PinHeader_2x07_P2.00mm_Horizontal_For_SeeedStudio
J2: 650906-5; 6509065
J3: 10029449-111RLF (HDMI A); HDMI_A_Amphenol_10029449-111
J4: A2541HWR-2x6P (Pmod 2x6 F R); PinSocket_2x06_P2.54mm_Horizontal
JAB1: ZTEX_AB-ztex_AB; PinHeader_2x32_P2.54mm_Vertical_For_SeeedStudio
JCD1: ZTEX_CD-ztex_CD; PinHeader_2x32_P2.54mm_Vertical_For_SeeedStudio
R1: 560; R_0603_1608Metric
R2: 1M 500V 1206; R_1206_3216Metric
R3, R4, R5, R6, R7, R8, R9, R10: 22; R_0402_1005Metric
R11, R12, R13, R14, R15, R16, R17: 10k; R_0603_1608Metric
S1: SSAJ110100; SW_SSAJ110100
U1, U2, U3, U4, U5, U6, U7, U8, U9, U10, U11, U13: SN74CB3T3245PWR; SOP65P640X120-20N
U12: TPD12S016PWR; SOP65P640X120-24N
U14: SN74LV1T125DCKR; SOT65P210X110-5N

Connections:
+3V3: C1.1, C2.1, C4.1, C5.1, C6.1, C7.1, C8.1, C9.1, C10.1, C11.1, C12.1, C13.1, C14.1, C15.1, C16.1, C17.1, C21.1, C22.1, C23.2, C24.1, J4.11, J4.12, JAB1.29, JAB1.30, JAB1.33, JAB1.34, JCD1.31, JCD1.32, JCD1.35, JCD1.36, R1.1, R13.1, R14.1, U1.20, U2.20, U3.20, U4.20, U5.20, U6.20, U7.20, U8.20, U9.20, U10.20, U11.20, U12.5, U12.12, U12.24, U13.20, U14.5
+5V: C3.1, C18.1, J2.A37, J2.B13, J2.B19, J2.B25, J2.B31, J2.B37, J2.C37, JAB1.1, JAB1.2, R16.1, R17.1, U12.11
/B2B/JTAG_VIO: J1.2, JAB1.63
/HDMI/HDMI_5V: C19.1, J3.18, U12.13
/HDMI/cec_b: J3.13, U12.7
/HDMI/hpd_b: J3.19, U12.10
/HDMI/scl_b: J3.15, U12.8
/HDMI/sda_b: J3.16, U12.9
/pmod/P56+: J4.7, R7.1
/pmod/P56-: J4.8, R3.2
/pmod/P78+: J4.5, R8.1
/pmod/P78-: J4.6, R4.2
/pmod/P910+: J4.3, R9.1
/pmod/P910-: J4.4, R5.2
/pmod/P1112+: J4.1, R10.1
/pmod/P1112-: J4.2, R6.2
A0: J2.C36, U10.3
A0_3V3: JCD1.6, U10.17
A1: J2.B36, U10.4
A1_3V3: JCD1.5, U10.16
A2: J2.A36, U10.5
A2_3V3: JCD1.8, U10.15
A3: J2.C35, U10.6
A3_3V3: JCD1.7, U10.14
A4: J2.B35, U10.7
A4_3V3: JCD1.10, U10.13
A5: J2.A35, U10.8
A5_3V3: JCD1.9, U10.12
A6: J2.C34, U10.9
A6_3V3: JCD1.12, U10.11
A7: J2.A34, U9.2
A7_3V3: JCD1.11, U9.18
A8: J2.C33, U9.3
A8_3V3: JCD1.14, U9.17
A9: J2.B33, U9.4
A9_3V3: JAB1.6, U9.16
A10: J2.A33, U9.5
A10_3V3: JAB1.5, U9.15
A11: J2.C32, U9.6
A11_3V3: JAB1.8, U9.14
A12: J2.B32, U9.7
A12_3V3: JAB1.7, U9.13
A13: J2.A32, U9.8
A13_3V3: JAB1.10, U9.12
A14: J2.C31, U9.9
A14_3V3: JAB1.9, U9.11
A15: J2.A31, U8.2
A15_3V3: JAB1.12, U8.18
A16: J2.C30, U8.3
A16_3V3: JAB1.11, U8.17
A17: J2.B30, U8.4
A17_3V3: JAB1.14, U8.16
A18: J2.A30, U8.5
A18_3V3: JAB1.13, U8.15
A19: J2.C29, U8.6
A19_3V3: JAB1.16, U8.14
A20: J2.B29, U8.7
A20_3V3: JAB1.15, U8.13
A21: J2.A29, U8.8
A21_3V3: JAB1.18, U8.12
A22: J2.C28, U8.9
A22_3V3: JAB1.17, U8.11
A23: J2.A28, U7.2
A23_3V3: JAB1.19, U7.18
A24: J2.C27, U7.3
A24_3V3: JAB1.22, U7.17
A25: J2.B27, U7.4
A25_3V3: JAB1.21, U7.16
A26: J2.A27, U7.5
A26_3V3: JAB1.23, U7.15
A27: J2.C26, U7.6
A27_3V3: JAB1.24, U7.14
A28: J2.B26, U7.7
A28_3V3: JAB1.25, U7.13
A29: J2.A26, U7.8
A29_3V3: JAB1.26, U7.12
A30: J2.C25, U7.9
A30_3V3: JAB1.27, U7.11
A31: J2.A25, U6.2
A31_3V3: JAB1.28, U6.18
C16M: J2.C38, U13.8
C16M_3V3: JCD1.40, R5.1, U13.12
CACHE: J2.B2, U11.8
CACHE_3V3: JCD1.27, R12.1, U11.12
CPUCLK: J2.A38, U10.2
CPUCLK_3V3: JAB1.20, U10.18
D0: J2.A13, U4.2
D0_3V3: JCD1.48, U4.18
D1: J2.C13, U5.9
D1_3V3: JAB1.58, U5.11
D2: J2.A14, U5.8
D2_3V3: JCD1.47, U5.12
D3: J2.B14, U5.7
D3_3V3: JAB1.55, U5.13
D4: J2.C14, U5.6
D4_3V3: JAB1.56, U5.14
D5: J2.A15, U5.5
D5_3V3: JCD1.46, U5.15
D6: J2.B15, U5.4
D6_3V3: JAB1.53, U5.16
D7: J2.C15, U5.3
D7_3V3: JAB1.54, U5.17
D8: J2.A16, U5.2
D8_3V3: JCD1.45, U5.18
D9: J2.C16, U2.9
D9_3V3: JAB1.51, U2.11
D10: J2.A17, U2.8
D10_3V3: JAB1.52, U2.12
D11: J2.B17, U2.7
D11_3V3: JCD1.44, U2.13
D12: J2.C17, U2.6
D12_3V3: JAB1.49, U2.14
D13: J2.A18, U2.5
D13_3V3: JAB1.50, U2.15
D14: J2.B18, U2.4
D14_3V3: JCD1.43, U2.16
D15: J2.C18, U2.3
D15_3V3: JAB1.47, U2.17
D16: J2.A19, U2.2
D16_3V3: JAB1.48, U2.18
D17: J2.C19, U1.9
D17_3V3: JCD1.42, U1.11
D18: J2.A20, U1.8
D18_3V3: JAB1.45, U1.12
D19: J2.B20, U1.7
D19_3V3: JAB1.46, U1.13
D20: J2.C20, U1.6
D20_3V3: JCD1.41, U1.14
D21: J2.A21, U1.5
D21_3V3: JAB1.43, U1.15
D22: J2.B21, U1.4
D22_3V3: JAB1.44, U1.16
D23: J2.C21, U1.3
D23_3V3: JAB1.41, U1.17
D24: J2.A22, U1.2
D24_3V3: JAB1.42, U1.18
D25: J2.C22, U6.9
D25_3V3: JAB1.39, U6.11
D26: J2.A23, U6.8
D26_3V3: JAB1.40, U6.12
D27: J2.B23, U6.7
D27_3V3: JAB1.37, U6.13
D28: J2.C23, U6.6
D28_3V3: JAB1.38, U6.14
D29: J2.A24, U6.5
D29_3V3: JAB1.35, U6.15
D30: J2.B24, U6.4
D30_3V3: JAB1.36, U6.16
D31: J2.C24, U6.3
D31_3V3: JCD1.29, U6.17
FC0: J2.C11, U4.5
FC0_3V3: JAB1.59, U4.15
FC1: J2.B11, U4.7
FC1_3V3: JCD1.50, U4.13
FC2: J2.A11, U4.8
FC2_3V3: JCD1.51, U4.12
FPGA_JTAG_TCK: J1.6, JAB1.62
FPGA_JTAG_TDI: J1.10, JAB1.61
FPGA_JTAG_TDO: J1.8, JCD1.61
FPGA_JTAG_TMS: J1.4, JCD1.62
GND: C1.2, C2.2, C3.2, C4.2, C5.2, C6.2, C7.2, C8.2, C9.2, C10.2, C11.2, C12.2, C13.2, C14.2, C15.2, C16.2, C17.2, C18.2, C19.2, C20.2, C21.2, C22.2, C23.1, C24.2, D1.1, J1.1, J1.3, J1.5, J1.7, J1.9, J1.11, J1.13, J2.A39, J2.B16, J2.B22, J2.B28, J2.B34, J2.B39, J2.C39, J3.2, J3.5, J3.8, J3.11, J3.17, J4.9, J4.10, JAB1.3, JAB1.4, JAB1.31, JAB1.32, JAB1.64, JCD1.3, JCD1.4, JCD1.33, JCD1.34, JCD1.63, JCD1.64, R2.2, R11.2, R12.2, R15.1, U1.10, U1.19, U2.10, U2.19, U3.10, U3.19, U4.3, U4.10, U4.19, U5.10, U5.19, U6.10, U6.19, U7.10, U7.19, U8.10, U8.19, U9.10, U9.19, U10.10, U10.19, U11.3, U11.5, U11.7, U11.9, U11.10, U11.19, U12.6, U13.10, U14.2, U14.3
HDMI_CLK+: J3.10, JCD1.21, U12.16
HDMI_CLK-: J3.12, JCD1.23, U12.15
HDMI_D0+: J3.7, JCD1.20, U12.18
HDMI_D0-: J3.9, JCD1.22, U12.17
HDMI_D1+: J3.4, JCD1.17, U12.21
HDMI_D1-: J3.6, JCD1.19, U12.20
HDMI_D2+: J3.1, JCD1.16, U12.23
HDMI_D2-: J3.3, JCD1.18, U12.22
unnamed: D1.2, R1.2
unnamed: R14.2, S1.2
unnamed: R15.2, S1.1
PMOD-56+: JCD1.24, R7.2, U13.13
PMOD-56-: JCD1.26, R3.1, U13.17
PMOD-78+: JCD1.28, R8.2, U13.11
PMOD-78-: JCD1.30, R4.1, U13.15
PMOD-910+: JCD1.38, R9.2, U13.18
PMOD-1112+: JCD1.39, R10.2, U13.14
PMOD-1112-: JCD1.37, R6.1, U13.16
SHIELD: C20.1, H5.1, J3.SH, R2.1
SIZ0: J2.B9, U3.2
SIZ0_3V3: JCD1.53, U3.18
SIZ1: J2.A9, U3.3
SIZ1_3V3: JCD1.54, U3.17
~AS: J2.C9, U4.9
~AS_3V3: JCD1.52, U4.11
~BERR: J2.B12, U4.4
~BERR_3V3: JAB1.60, U4.16
~BG: J2.B10, U13.4
~BGACK: J2.A10, U13.2
~BR: J2.C10, U13.6
~CBACK: J2.B7, U11.2
~CBACK_3V3: JCD1.13, U11.18
~CBREQ: J2.C7, U11.4
~CBREQ_3V3: JCD1.15, U11.16
~CIOUT: J2.A6, U11.6
~CIOUT_3V3: JCD1.25, U11.14
~DS: J2.B6, U3.8
~DSACK0: J2.B8, U3.5
~DSACK0_3V3: JCD1.56, U3.15
~DSACK1: J2.A8, U3.6
~DSACK1_3V3: JCD1.57, U3.14
~DS_3V3: JCD1.59, U3.12
~FPU: J2.A2, U13.9
~HALT: J2.C12, U14.4
~HALT_3V3: JAB1.57, R11.1, U14.1
~IRQ1: J2.C4, U3.9
~IRQ1_3V3: JCD1.60, R13.2, U3.11
~IRQ2: J2.B4, R16.2, U13.3
~IRQ3: J2.A4, R17.2, U13.7
~MASTER_OE: S1.C, U13.19
~RBV: J2.A1, U13.5
~RESET: J2.A12, U4.6
~RESET_3V3: JCD1.49, U4.14
~RW: J2.C8, U3.4
~RW_3V3: JCD1.55, U3.16
~STERM: J2.A7, U3.7
~STERM_3V3: JCD1.58, U3.13

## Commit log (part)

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2023-04-01 import draft to GH
2023-04-01 start work on simul
2023-04-01 readme
2023-04-01 rework /HALT
2023-04-01 change of pins
2023-04-01 handle /halt, wait for locked PLL
2023-05-16 cleanup DRC
2023-05-27 extra stuff
2023-05-27 3V3 SRAM draft
2023-05-28 missing file
2023-06-03 pcb upd
2023-06-03 connect rbv to last pmod pin
2023-06-03 some rerouting
2023-06-04 minro cleanups
2023-06-06 some pull-(up,down)s
2023-06-13 catching up with PCB
2023-06-25 early bringup
2023-06-25 cleanup, map memory in superslot (for now)
2023-06-25 more mapping, fix partial write
2023-06-26 write FIFO
2023-07-01 first attempt at burst ; but so far mapping through TT0 doesn't seem to enable burst (though regular accesses work)
2023-07-01 some fixes, but burst doesn't work properly
2023-07-02 fix burst mode
2023-07-23 push update that supports memory mode, with tons of leftovers debug code
2023-07-23 move memory expansion mapping back to (instead of -bash8)
2023-08-15 first go at crypto co-pro, copro iface seems OK but crypto still wrong (endianess?)
2023-08-15 oups, backward inputs
2023-08-15 fx some endianess
2023-08-15 fix endianess, LGTM
2023-08-15 just in case
2023-08-17 optional in-copro state
2023-08-19 mmmm, FloCoPo?
2023-08-20 less code duplication
2023-08-20 fixes
2023-08-20 fp-to-fp
2023-08-20 reorg
2023-08-20 div, sub (as a+(-b)), neg, abs, missing files
2023-08-20 mfmovecr
2023-09-16 license
2023-11-18 move some of board platform stuff to common
2023-11-19 move stuff in common as for the others; need to work on rd68891's decrypt stuff
2023-12-02 debug stuff
2023-12-02 upd common
2023-12-02 add ref
2023-12-02 subdir
2024-02-02 pmod orientation
2024-02-17 catch-up for progammable clock
2024-02-23 drop moved file
2024-02-24 updat e REF
2024-02-24 uppdate/expand flopoco files, flag instruciton not implemented on '040
2024-05-18 IIfx support (needs its own bitstream), board-based name
2024-05-18 IIfx support, fast slew on D/STERM, stronger drive on STERM, need to think more about this...
2024-09-01 down-conversion from Motorola's FP80 to IEEE FP32/FP64 (from patched flopoco)
2024-09-07 fmovem (data register)
2024-09-07 move const table to native flopoco format
2024-09-08 some FPSR bits, plus first draft of conditionals (untested)
2024-09-14 some level of support for FPSR (w/ minimal branch testing done)
2024-09-14 committing fixed OutputIEEE
2024-09-14 fix multi-ctrl order, implement ea->ctrl dialog
2024-09-15 pseudo-save/restore
2024-09-22 react properly to operand partial write
2024-09-22 fmove to fp w/ integer input (using flopoco 4.1.1 Fix2FP operator)
2024-09-24 longword output (byte/word not rounded properly)
2025-09-06 timing file for testing
2025-09-06 mmm, BCD?
2026-01-06 comments
2026-02-22 From Template
2026-03-21 fix BoM
2026-03-25 minor fix
2026-03-25 various updates
2026-03-25 V3.0 board files
2026-03-25 do files, submodule
2026-03-25 produciton files
2026-03-25 status
2026-03-28 update v1 do
2026-03-28 unify leds naming with IIsiA7 Mini
2026-03-28 cleanup
2026-03-28 grr, fix pin order
2026-03-29 minor cleanups

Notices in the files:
IIsiA7_Mini/IIsiA7_Mini.kicad_pcb:
© 2026 Romain Dolbeau
